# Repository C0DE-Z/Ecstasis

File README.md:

# Ecstasis Mk2
 *to stand outside oneself*

A Fuzz pedal based after the Electro-Harmonix Big Muff Pi V7 (Green Russian)

Powered by 9v battery or DC input 
using cheap and easy to source parts, trying to replacate the sound of the orginal somewhat closely. 

## Improvments from the Mk1
- Optmized track width for 9v powerline
- Fixxed Footprint for the 1/4 inch audio jacking being inverted
- Optimized Part location 
- Lowered VIA count
- Added silkscreen prints to show what each pot does, and for what is in and out.

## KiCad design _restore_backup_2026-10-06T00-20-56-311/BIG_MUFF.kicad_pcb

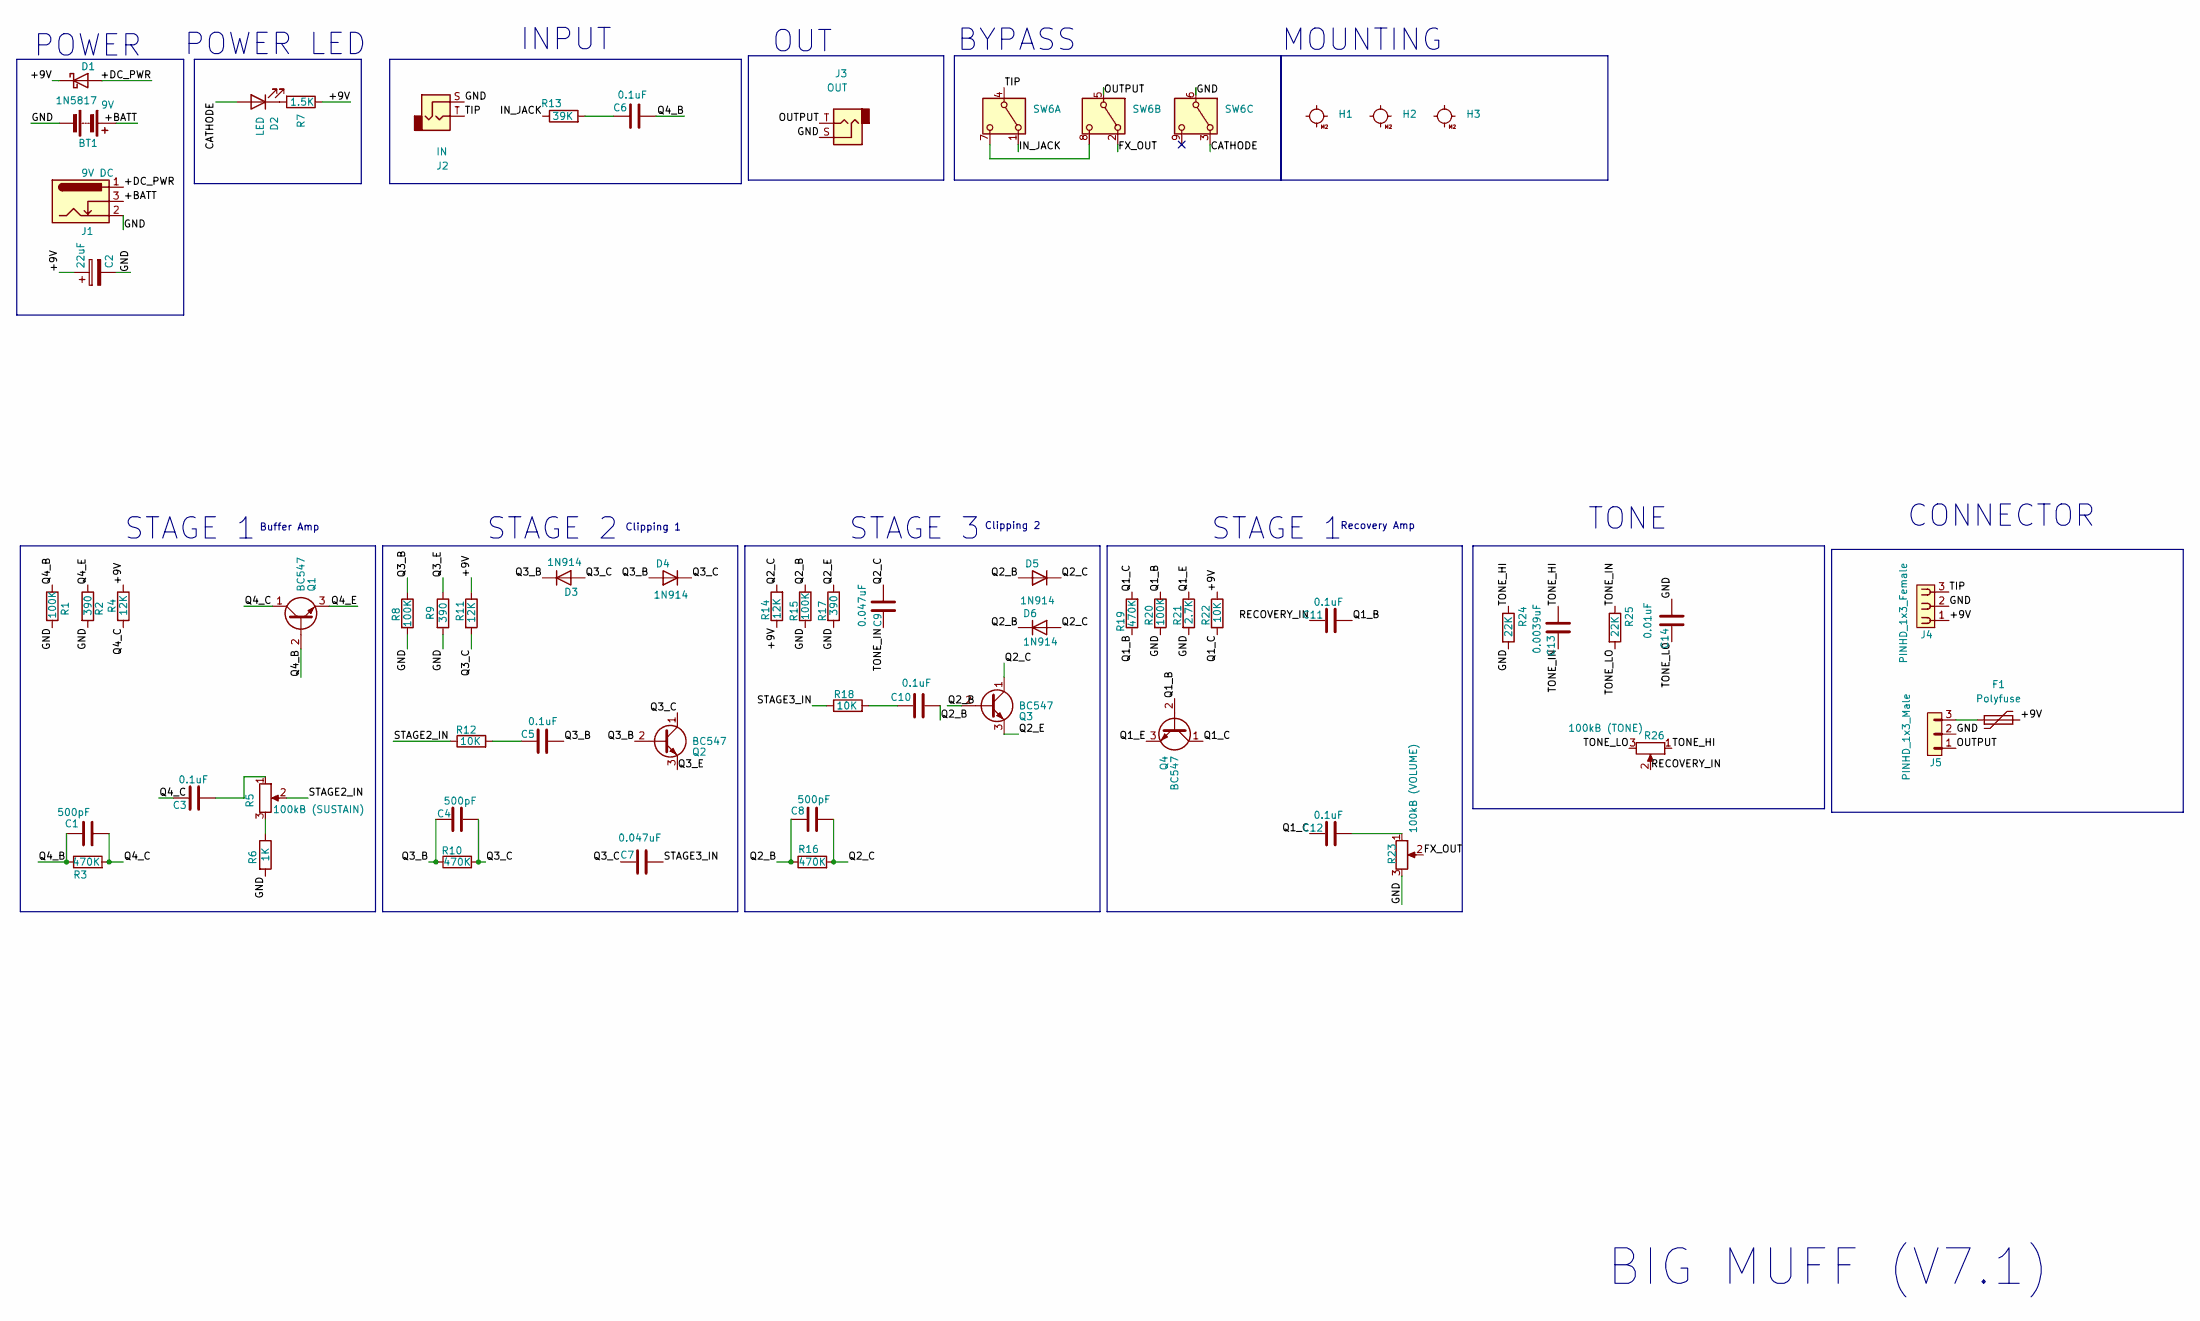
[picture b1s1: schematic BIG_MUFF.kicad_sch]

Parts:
BT1: 9V; SolderWire-0.75sqmm_1x02_P4.8mm_D1.25mm_OD2.3mm
C1, C4, C8: 500pF; C_Disc_D5.0mm_W2.5mm_P2.50mm
C2: 22uF; CP_Radial_D5.0mm_P2.00mm
C3, C5, C6, C10, C11, C12: 0.1uF; C_Rect_L7.0mm_W2.5mm_P5.00mm
C7, C9: 0.047uF; C_Rect_L7.0mm_W2.5mm_P5.00mm
C13: 0.0039uF; C_Rect_L7.0mm_W2.5mm_P5.00mm
C14: 0.01uF; C_Rect_L7.0mm_W2.5mm_P5.00mm
D1: 1N5817; D_DO-35_SOD27_P7.62mm_Horizontal
D2: LED; LED_D3.0mm
D3, D4, D6: 1N914; D_DO-35_SOD27_P7.62mm_Horizontal
D5: 1N914; D_DO-41_SOD81_P7.62mm_Horizontal
F1: Polyfuse; Fuse_Bourns_MF-RHT100
H1, H2, H3: MountingHole_M2
J1: 9V DC; BarrelJack_Horizontal
J2: IN; J_6.35mm_NMJ4HCD2_Custom
J3: OUT; J_6.35mm_NMJ4HCD2_Custom
J4: PINHD_1x3_Female; PinSocket_1x03_P2.54mm_Horizontal
J5: PINHD_1x3_Male; PinSocket_1x03_P2.54mm_Horizontal
Q1, Q2, Q3, Q4: BC547; TO-92_Inline
R1, R8, R15, R20: 100K; R_Axial_DIN0207_L6.3mm_D2.5mm_P7.62mm_Horizontal
R2, R9, R17: 390; R_Axial_DIN0207_L6.3mm_D2.5mm_P7.62mm_Horizontal
R3, R10, R16, R19: 470K; R_Axial_DIN0207_L6.3mm_D2.5mm_P7.62mm_Horizontal
R4, R11, R14: 12K; R_Axial_DIN0207_L6.3mm_D2.5mm_P7.62mm_Horizontal
R5: 100kB (SUSTAIN); Potentiometer_Alpha_RD901F-40-00D_Single_Vertical
R6: 1K; R_Axial_DIN0207_L6.3mm_D2.5mm_P7.62mm_Horizontal
R7: 1.5K; R_Axial_DIN0207_L6.3mm_D2.5mm_P7.62mm_Horizontal
R12, R18, R22: 10K; R_Axial_DIN0207_L6.3mm_D2.5mm_P7.62mm_Horizontal
R13: 39K; R_Axial_DIN0207_L6.3mm_D2.5mm_P7.62mm_Horizontal
R21: 2.7K; R_Axial_DIN0207_L6.3mm_D2.5mm_P7.62mm_Horizontal
R23: 100kB (VOLUME); Potentiometer_Alpha_RD901F-40-00D_Single_Vertical
R24, R25: 22K; R_Axial_DIN0207_L6.3mm_D2.5mm_P7.62mm_Horizontal
R26: 100kB (TONE); Potentiometer_Alpha_RD901F-40-00D_Single_Vertical
SW6: SW_3PDT_Footswitch; SW_3PDT_Footswitch_9Pin_Custom

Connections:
/+9V: C2.1, D1.1 (K), F1.2, J4.1, R4.1, R7.1, R11.1, R14.1, R22.1
/+BATT: BT1.1 (+), J1.3
/+DC_PWR: D1.2 (A), J1.1
/CATHODE: D2.2 (A), SW6.3 (A3)
/FX_OUT: R23.2, SW6.2 (A2)
/GND: BT1.2 (-), C2.2, C14.2, J1.2, J2.S, J3.S, J4.2, J5.2, R1.2, R2.2, R6.2, R8.2, R9.2, R15.2, R17.2, R20.2, R21.2, R23.3, R24.2, SW6.6 (COM3)
/IN_JACK: R13.1, SW6.1 (A1)
/OUTPUT: J3.T, J5.1, SW6.5 (COM2)
/Q1_B: C11.2, Q4.2 (B), R19.1, R20.1
/Q1_C: C12.1, Q4.1 (C), R19.2, R22.2
/Q1_E: Q4.3 (E), R21.1
/Q2_B: C8.1, C10.2, D5.2 (A), D6.1 (K), Q3.2 (B), R15.1, R16.1
/Q2_C: C8.2, C9.1, D5.1 (K), D6.2 (A), Q3.1 (C), R14.2, R16.2
/Q2_E: Q3.3 (E), R17.1
/Q3_B: C4.1, C5.2, D3.1 (K), D4.2 (A), Q2.2 (B), R8.1, R10.1
/Q3_C: C4.2, C7.1, D3.2 (A), D4.1 (K), Q2.1 (C), R10.2, R11.2
/Q3_E: Q2.3 (E), R9.1
/Q4_B: C1.1, C6.2, Q1.2 (B), R1.1, R3.1
/Q4_C: C1.2, C3.1, Q1.1 (C), R3.2, R4.2
/Q4_E: Q1.3 (E), R2.1
/RECOVERY_IN: C11.1, R26.2
/STAGE2_IN: R5.2, R12.1
/STAGE3_IN: C7.2, R18.1
/TIP: J2.T, J4.3, SW6.4 (COM1)
/TONE_HI: C13.2, R24.1, R26.1
/TONE_IN: C9.2, C13.1, R25.1
/TONE_LO: C14.1, R25.2, R26.3
unnamed: C3.2, R5.1
unnamed: C5.1, R12.2
unnamed: C6.1, R13.2
unnamed: C10.1, R18.2
unnamed: C12.2, R23.1
unnamed: D2.1 (K), R7.2
unnamed: F1.1, J5.3
unnamed: R5.3, R6.1
unnamed: SW6.7 (B1), SW6.8 (B2)

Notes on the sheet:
Recovery Amp
POWER
BIG MUFF (V7.1)
Buffer Amp
Clipping 2
CONNECTOR
INPUT
POWER LED
OUT
BYPASS
Clipping 1
STAGE 1
STAGE 3
MOUNTING
STAGE 2
TONE

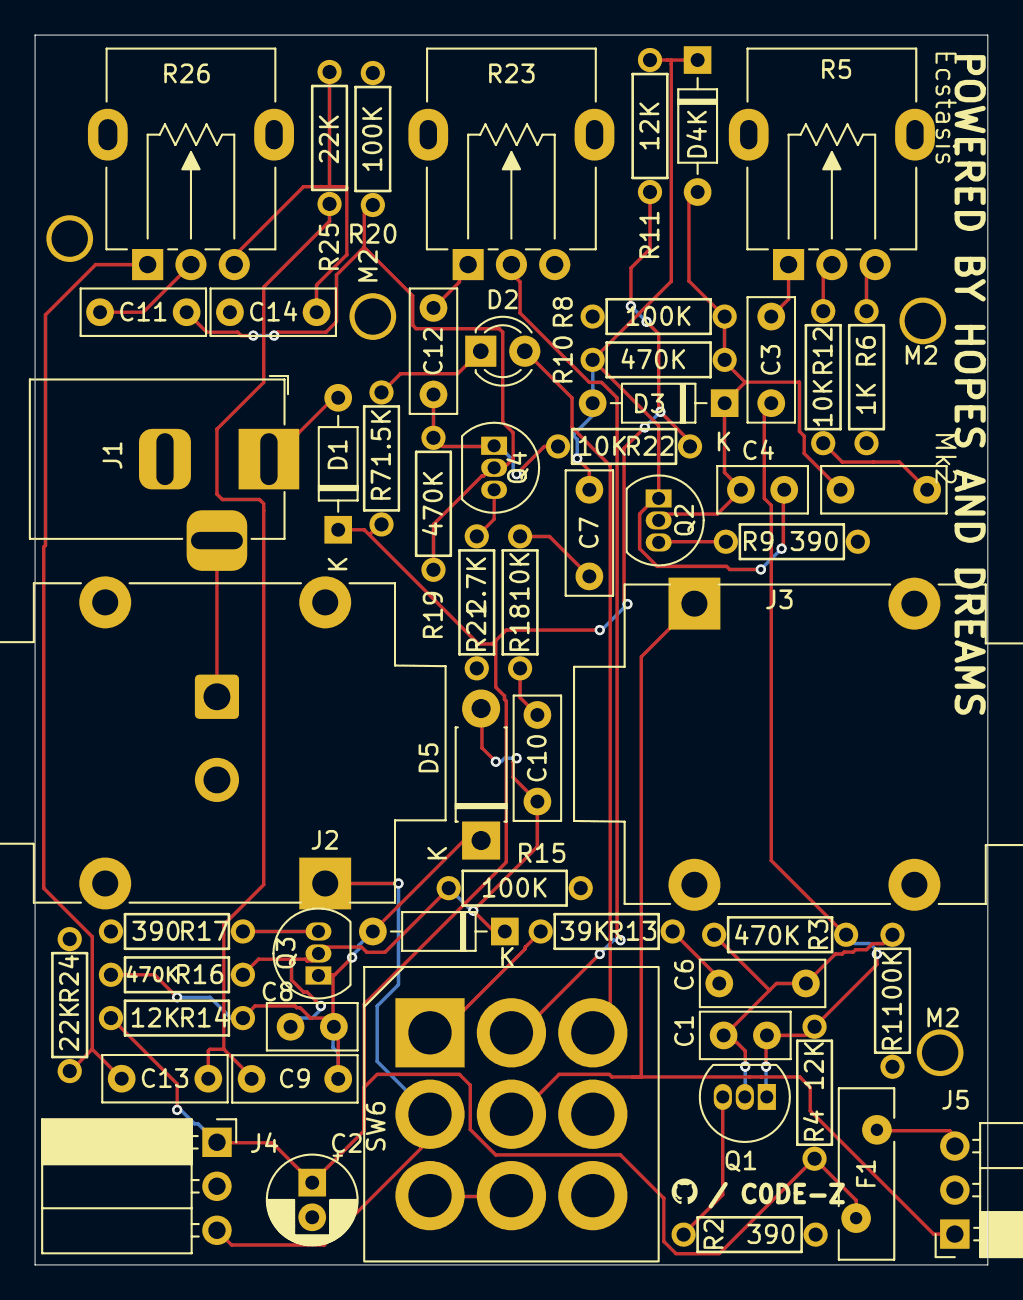
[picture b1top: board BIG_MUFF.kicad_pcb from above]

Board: 2 copper layers, 55.0 x 71.0 mm, 61 parts (1 on the bottom side), 36 nets.

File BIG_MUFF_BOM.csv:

Item,Category,Designators,Qty,Value / Part Name,Package / Footprint,Recommended Part / Sourcing,Est. Cost ($)
1,Potentiometer,R5,1,100k Linear (B100K),Alpha 9mm Vertical (RD901F),Alpha RD901F-40-15R1-B100K,1.00
2,Potentiometer,R23,1,100k Log/Linear (A100K/B100K),Alpha 9mm Vertical (RD901F),Alpha RD901F-40-15R1-B100K (Volume),1.00
3,Potentiometer,R26,1,100k Linear (B100K),Alpha 9mm Vertical (RD901F),Alpha RD901F-40-15R1-B100K (Tone),1.00
4,Footswitch,SW6,1,3PDT Stomp Switch,Custom 9-Pin 4.7mm Pitch THT,Standard Blue 3PDT 9-pin Latching Switch,3.00
5,Audio Jack,J2,1,"1/4"" Mono Jack (IN)",Neutrik NMJ4HCD2 Custom (1.5mm drill),Neutrik / Rean NMJ4HCD2,1.50
6,Audio Jack,J3,1,"1/4"" Mono Jack (OUT)",Neutrik NMJ4HCD2 Custom (1.5mm drill),Neutrik / Rean NMJ4HCD2,1.50
7,DC Jack,J1,1,2.1mm DC Power Jack,Barrel Jack Horizontal THT,2.1mm x 5.5mm PCB Barrel Jack,0.50
8,Battery,BT1,1,9V Battery Snap,Wire Pads 4.8mm Pitch,Heavy Duty 9V Battery Snap Clip,0.40
9,Reed Switch,"SW4, SW5",2,14mm Reed Switch,SW_Reed_14mm_Custom (20mm pitch),Standex KSK-1A80-1015 / KSK 14mm,1.20
10,Pin Headers,"J4, J5",2,1x3 Header / Socket,2.54mm Pitch 1x3 THT,Standard 2.54mm 1x3 Pin Header / Socket,0.20
11,Transistor,"Q1, Q2, Q3, Q4",4,NPN Transistor,TO-92 Inline THT,BC547B / 2N5088 / NOS Russian KT3102E,0.60
12,Diode,"D3, D4, D5, D6",4,1N914 / 1N4148,DO-35 Axial THT,1N914 or 1N4148 Silicon Diode,0.20
13,Diode,D1,1,1N5817,DO-41 Axial THT,1N5817 Schottky Protection Diode,0.10
14,LED,D2,1,3mm / 5mm Red LED,LED_D3.0mm THT,Standard 3mm Red LED,0.15
15,Fuse,F1,1,Polyfuse 100mA,Radial THT (MF-RHT100),Bourns MF-RHT100 PTC Resettable Fuse,0.25
16,Resistor,"R2, R9, R17",3,390 Ω,Axial DIN0207 (7.62mm pitch),1/4W 1% Metal Film / Carbon Film,0.15
17,Resistor,R6,1,1 kΩ,Axial DIN0207 (7.62mm pitch),1/4W 1% Metal Film / Carbon Film,0.05
18,Resistor,R7,1,1.5 kΩ,Axial DIN0207 (7.62mm pitch),1/4W 1% Metal Film / Carbon Film,0.05
19,Resistor,R21,1,2.7 kΩ,Axial DIN0207 (7.62mm pitch),1/4W 1% Metal Film / Carbon Film,0.05
20,Resistor,"R12, R18, R22",3,10 kΩ,Axial DIN0207 (7.62mm pitch),1/4W 1% Metal Film / Carbon Film,0.15
21,Resistor,"R4, R11, R14",3,12 kΩ,Axial DIN0207 (7.62mm pitch),1/4W 1% Metal Film / Carbon Film,0.15
22,Resistor,"R24, R25",2,22 kΩ,Axial DIN0207 (7.62mm pitch),1/4W 1% Metal Film / Carbon Film,0.10
23,Resistor,R13,1,39 kΩ,Axial DIN0207 (7.62mm pitch),1/4W 1% Metal Film / Carbon Film,0.05
24,Resistor,"R1, R8, R15, R20",4,100 kΩ,Axial DIN0207 (7.62mm pitch),1/4W 1% Metal Film / Carbon Film,0.20
25,Resistor,"R3, R10, R16, R19",4,470 kΩ,Axial DIN0207 (7.62mm pitch),1/4W 1% Metal Film / Carbon Film,0.20
26,Capacitor,"C1, C4, C8",3,500 pF,Ceramic Disc 2.5mm Pitch,500pF 50V Ceramic Disc (or Silver Mica),0.30
27,Capacitor,C13,1,0.0039 µF (3.9nF),Box Film 5.0mm Pitch,3.9nF 63V/100V PET Film (Panasonic/WIMA),0.25
28,Capacitor,C14,1,0.01 µF (10nF),Box Film 5.0mm Pitch,10nF 63V/100V PET Film (Panasonic/WIMA),0.20
29,Capacitor,"C7, C9",2,0.047 µF (47nF),Box Film 5.0mm Pitch,47nF 63V/100V PET Film (Panasonic/WIMA),0.40
30,Capacitor,"C3, C5, C6, C10, C11, C12",6,0.1 µF (100nF),Box Film 5.0mm Pitch,100nF 63V/100V PET Film (Panasonic/WIMA),1.20
31,Capacitor,C2,1,22 µF 16V+,Radial Electrolytic 2.0mm Pitch,22uF 25V Radial Electrolytic (Nichicon/Panasonic),0.15
